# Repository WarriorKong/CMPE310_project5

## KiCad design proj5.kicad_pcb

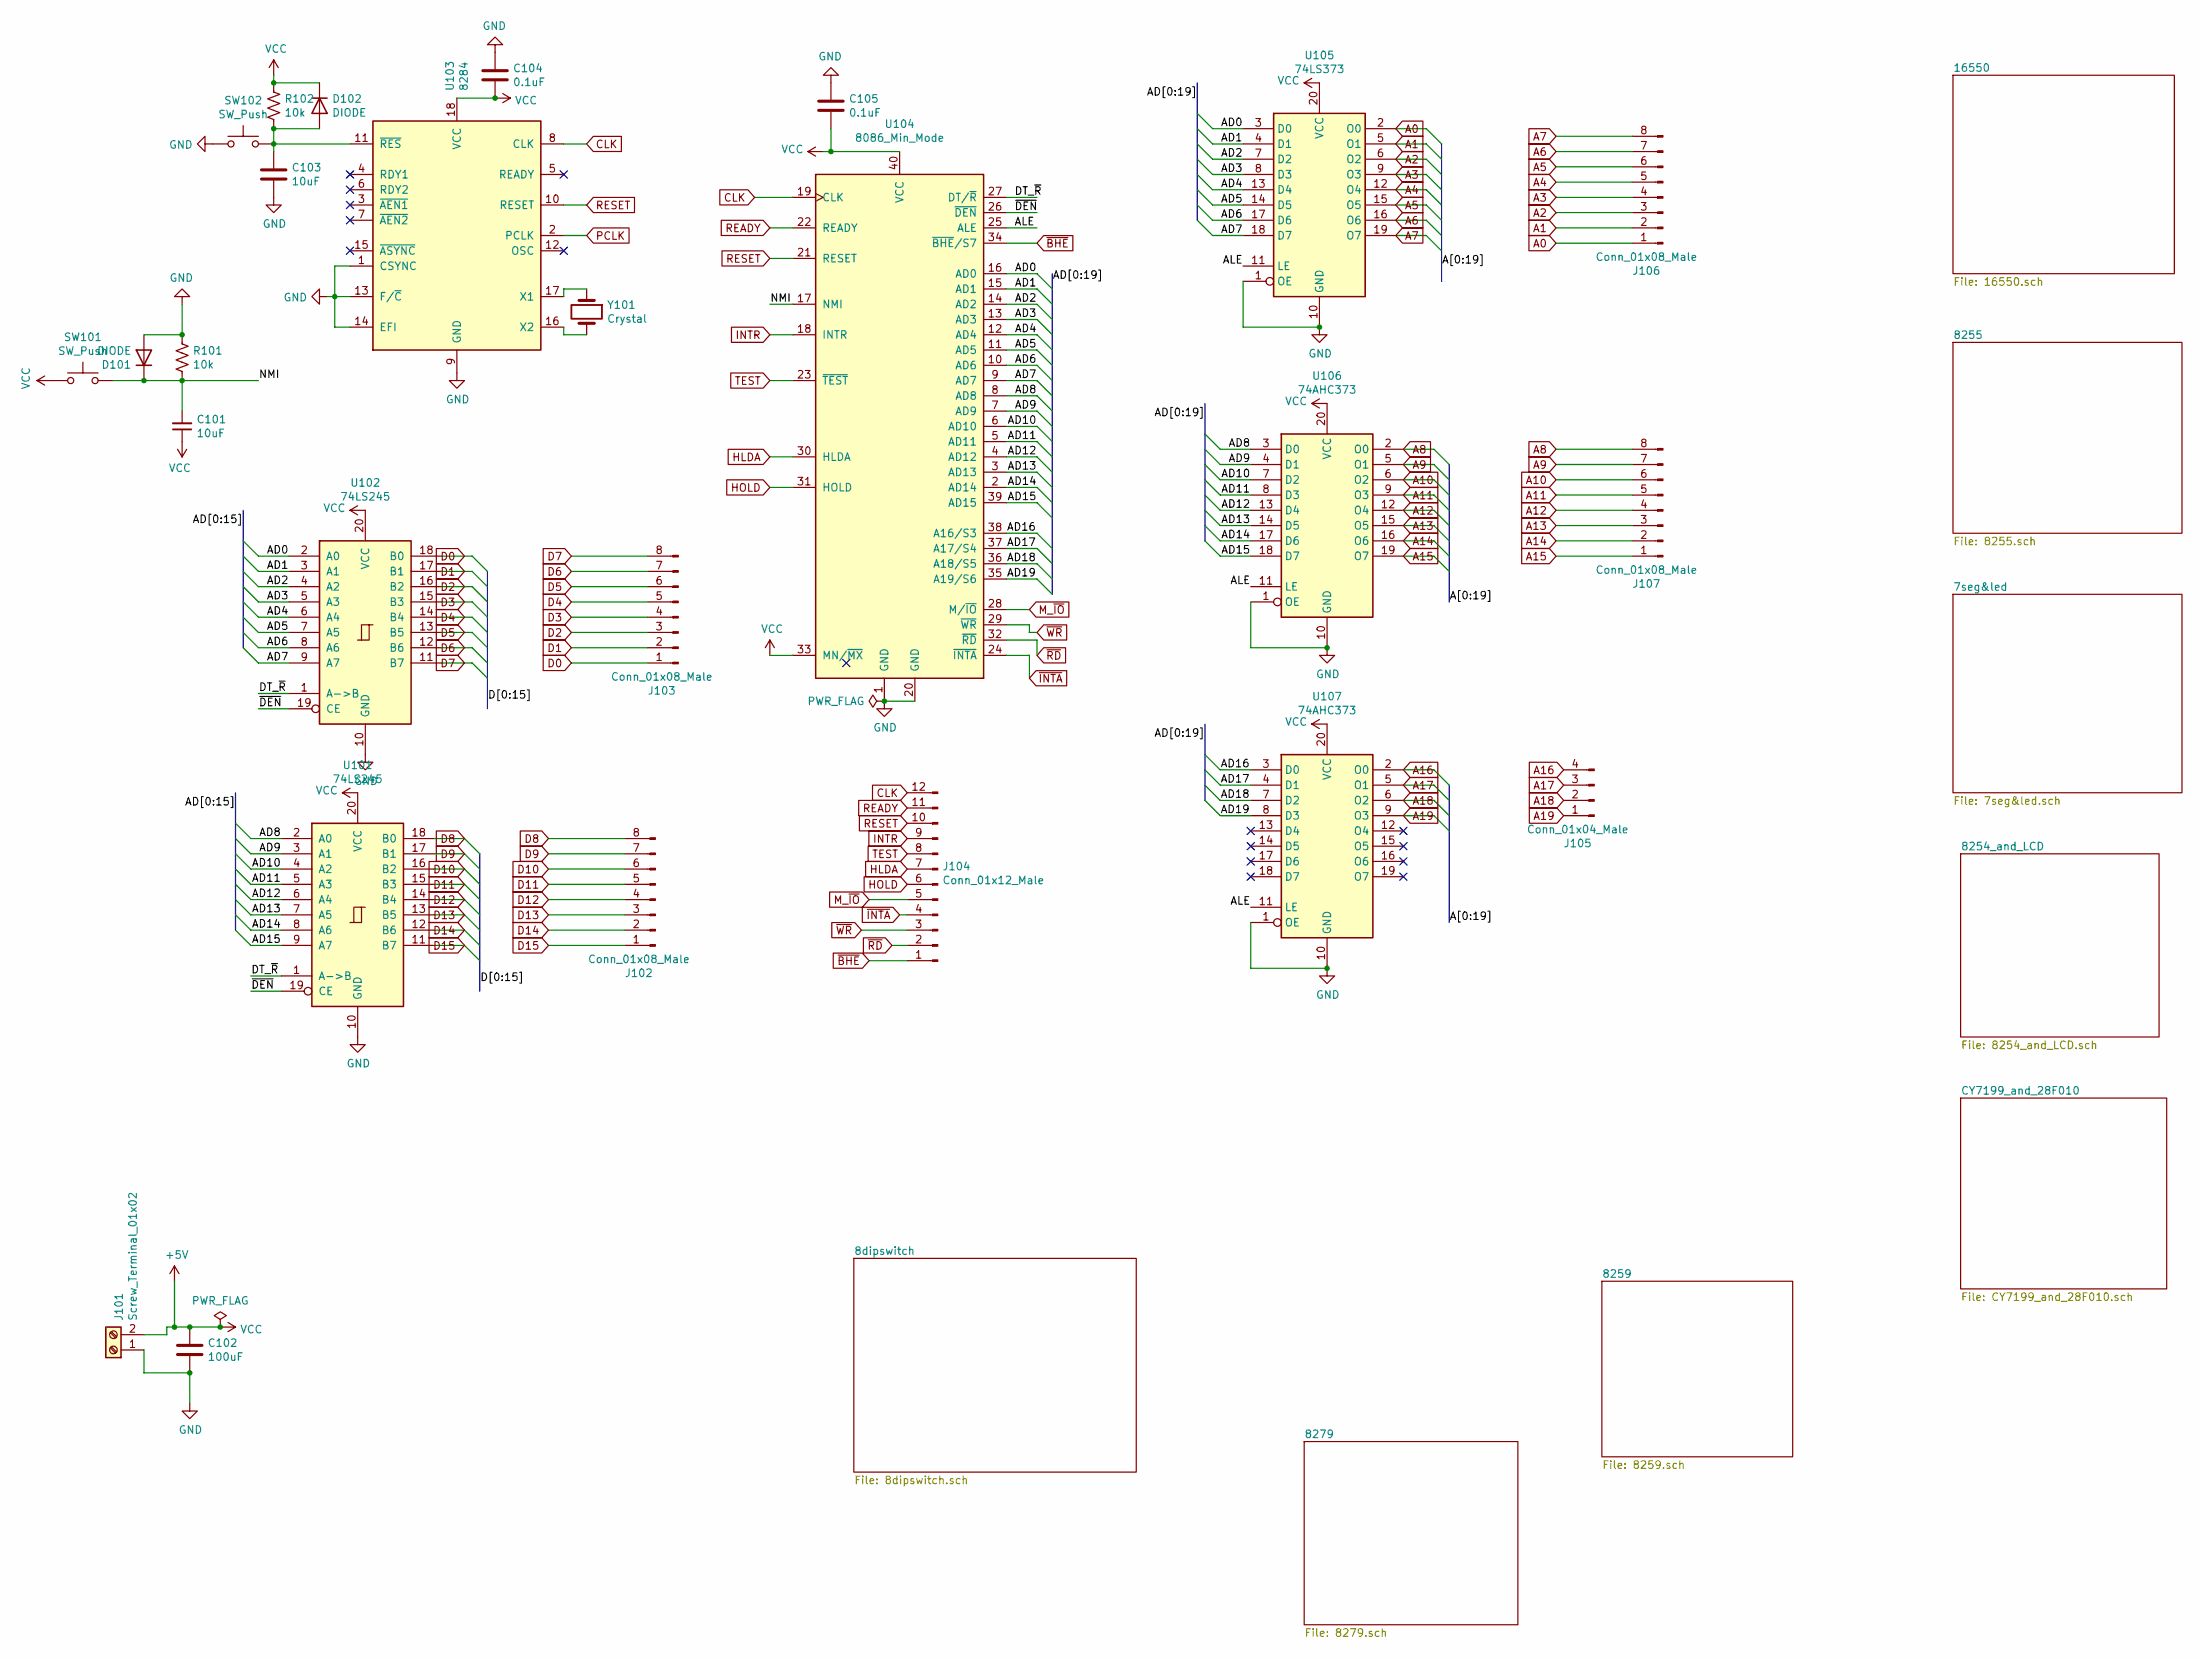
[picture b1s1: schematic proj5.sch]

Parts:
C101, C103: 10uF; CP_Elec_5x3
C102: 100uF; CP_Elec_8x5.4
C104, C105: 0.1uF; CP_Elec_3x5.3
D101, D102: DIODE; D_0402_1005Metric
J101: Screw_Terminal_01x02; TerminalBlock_Phoenix_MKDS-1,5-2-5.08_1x02_P5.08mm_Horizont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
J102, J103, J106, J107: Conn_01x08_Male; JST_GH_BM08B-GHS-TBT_1x08-1MP_P1.25mm_Vertical
J104: Conn_01x12_Male; JST_GH_BM12B-GHS-TBT_1x12-1MP_P1.25mm_Vertical
J105: Conn_01x04_Male; JST_GH_BM04B-GHS-TBT_1x04-1MP_P1.25mm_Vertical
R101, R102: 10k; R_0402_1005Metric
SW101, SW102: SW_Push; SW_SPST_B3U-1000P
U101, U102: 74LS245; DIP-20_W7.62mm_SMDSocket_SmallPads
U103: 8284; DIP-18_W7.62mm
U104: 8086_Min_Mode; DIP-40_W15.24mm
U105: 74LS373; DIP-20_W7.62mm_SMDSocket_SmallPads
U106, U107: 74AHC373; DIP-20_W7.62mm_SMDSocket_SmallPads
Y101: Crystal; Crystal_AT310_D3.0mm_L10.0mm_Horizontal

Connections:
+5V: C101.1, C102.1, C104.2, C105.2, D102.2 (K), J101.2, R102.1, SW101.1, U101.20 (VCC), U102.20 (VCC), U103.18 (VCC), U104.33 (MN/~MX~), U104.40 (VCC), U105.20 (VCC), U106.20 (VCC), U107.20 (VCC); also elsewhere on the board
/AD0: U102.2 (A0), U104.16 (AD0), U105.3 (D0)
/AD1: U102.3 (A1), U104.15 (AD1), U105.4 (D1)
/AD2: U102.4 (A2), U104.14 (AD2), U105.7 (D2)
/AD3: U102.5 (A3), U104.13 (AD3), U105.8 (D3)
/AD4: U102.6 (A4), U104.12 (AD4), U105.13 (D4)
/AD5: U102.7 (A5), U104.11 (AD5), U105.14 (D5)
/AD6: U102.8 (A6), U104.10 (AD6), U105.17 (D6)
/AD7: U102.9 (A7), U104.9 (AD7), U105.18 (D7)
/AD8: U101.2 (A0), U104.8 (AD8), U106.3 (D0)
/AD9: U101.3 (A1), U104.7 (AD9), U106.4 (D1)
/AD10: U101.4 (A2), U104.6 (AD10), U106.7 (D2)
/AD11: U101.5 (A3), U104.5 (AD11), U106.8 (D3)
/AD12: U101.6 (A4), U104.4 (AD12), U106.13 (D4)
/AD13: U101.7 (A5), U104.3 (AD13), U106.14 (D5)
/AD14: U101.8 (A6), U104.2 (AD14), U106.17 (D6)
/AD15: U101.9 (A7), U104.39 (AD15), U106.18 (D7)
/AD16: U104.38 (A16/S3), U107.3 (D0)
/AD17: U104.37 (A17/S4), U107.4 (D1)
/AD18: U104.36 (A18/S5), U107.7 (D2)
/AD19: U104.35 (A19/S6), U107.8 (D3)
/ALE: U104.25 (ALE), U105.11 (LE), U106.11 (LE), U107.11 (LE)
/DT_~R: U101.1 (A->B), U102.1 (A->B), U104.27 (DT/~R~)
/NMI: C101.2, D101.2 (K), R101.2, SW101.2, U104.17 (NMI)
/~DEN: U101.19 (CE), U102.19 (CE), U104.26 (~DEN~)
A0: J106.1, U105.2 (O0); also elsewhere on the board
A1: J106.2, U105.5 (O1); also elsewhere on the board
A2: J106.3, U105.6 (O2); also elsewhere on the board
A3: J106.4, U105.9 (O3); also elsewhere on the board
A4: J106.5, U105.12 (O4); also elsewhere on the board
A5: J106.6, U105.15 (O5); also elsewhere on the board
A6: J106.7, U105.16 (O6); also elsewhere on the board
A7: J106.8, U105.19 (O7); also elsewhere on the board
A8: J107.8, U106.2 (O0); also elsewhere on the board
A9: J107.7, U106.5 (O1); also elsewhere on the board
A10: J107.6, U106.6 (O2); also elsewhere on the board
A11: J107.5, U106.9 (O3); also elsewhere on the board
A12: J107.4, U106.12 (O4); also elsewhere on the board
A13: J107.3, U106.15 (O5); also elsewhere on the board
A14: J107.2, U106.16 (O6); also elsewhere on the board
A15: J107.1, U106.19 (O7); also elsewhere on the board
A16: J105.4, U107.2 (O0); also elsewhere on the board
A17: J105.3, U107.5 (O1); also elsewhere on the board
A18: J105.2, U107.6 (O2); also elsewhere on the board
A19: J105.1, U107.9 (O3); also elsewhere on the board
CLK: J104.12, U103.8 (CLK), U104.19 (CLK)
D0: J103.1, U102.18 (B0); also elsewhere on the board
D1: J103.2, U102.17 (B1); also elsewhere on the board
D2: J103.3, U102.16 (B2); also elsewhere on the board
D3: J103.4, U102.15 (B3); also elsewhere on the board
D4: J103.5, U102.14 (B4); also elsewhere on the board
D5: J103.6, U102.13 (B5); also elsewhere on the board
D6: J103.7, U102.12 (B6); also elsewhere on the board
D7: J103.8, U102.11 (B7); also elsewhere on the board
D8: J102.8, U101.18 (B0)
D9: J102.7, U101.17 (B1)
D10: J102.6, U101.16 (B2)
D11: J102.5, U101.15 (B3)
D12: J102.4, U101.14 (B4)
D13: J102.3, U101.13 (B5)
D14: J102.2, U101.12 (B6)
D15: J102.1, U101.11 (B7)
GND: C102.2, C103.2, C104.1, C105.1, D101.1 (A), J101.1, R101.1, SW102.1, U101.10 (GND), U102.10 (GND), U103.1 (CSYNC), U103.9 (GND), U103.13 (F/~C~), U103.14 (EFI), U104.1 (GND), U104.20 (GND), U105.1 (OE), U105.10 (GND), U106.1 (OE), U106.10 (GND), U107.1 (OE), U107.10 (GND); also elsewhere on the board
HLDA: J104.7, U104.30 (HLDA)
HOLD: J104.6, U104.31 (HOLD)
INTR: J104.9, U104.18 (INTR); also elsewhere on the board
M_~IO: J104.5, U104.28 (M/~IO~); also elsewhere on the board
unnamed: C103.1, D102.1 (A), R102.2, SW102.2, U103.11 (~RES~)
unnamed: U103.16 (X2), Y101.2
unnamed: U103.17 (X1), Y101.1
PCLK: U103.2 (PCLK); also elsewhere on the board
READY: J104.11, U104.22 (READY)
RESET: J104.10, U103.10 (RESET), U104.21 (RESET); also elsewhere on the board
TEST: J104.8, U104.23 (~TEST~)
~BHE: J104.1, U104.34 (~BHE~/S7); also elsewhere on the board
~INTA: J104.4, U104.24 (~INTA~); also elsewhere on the board
~RD: J104.2, U104.32 (~RD~); also elsewhere on the board
~WR: J104.3, U104.29 (~WR~); also elsewhere on the board

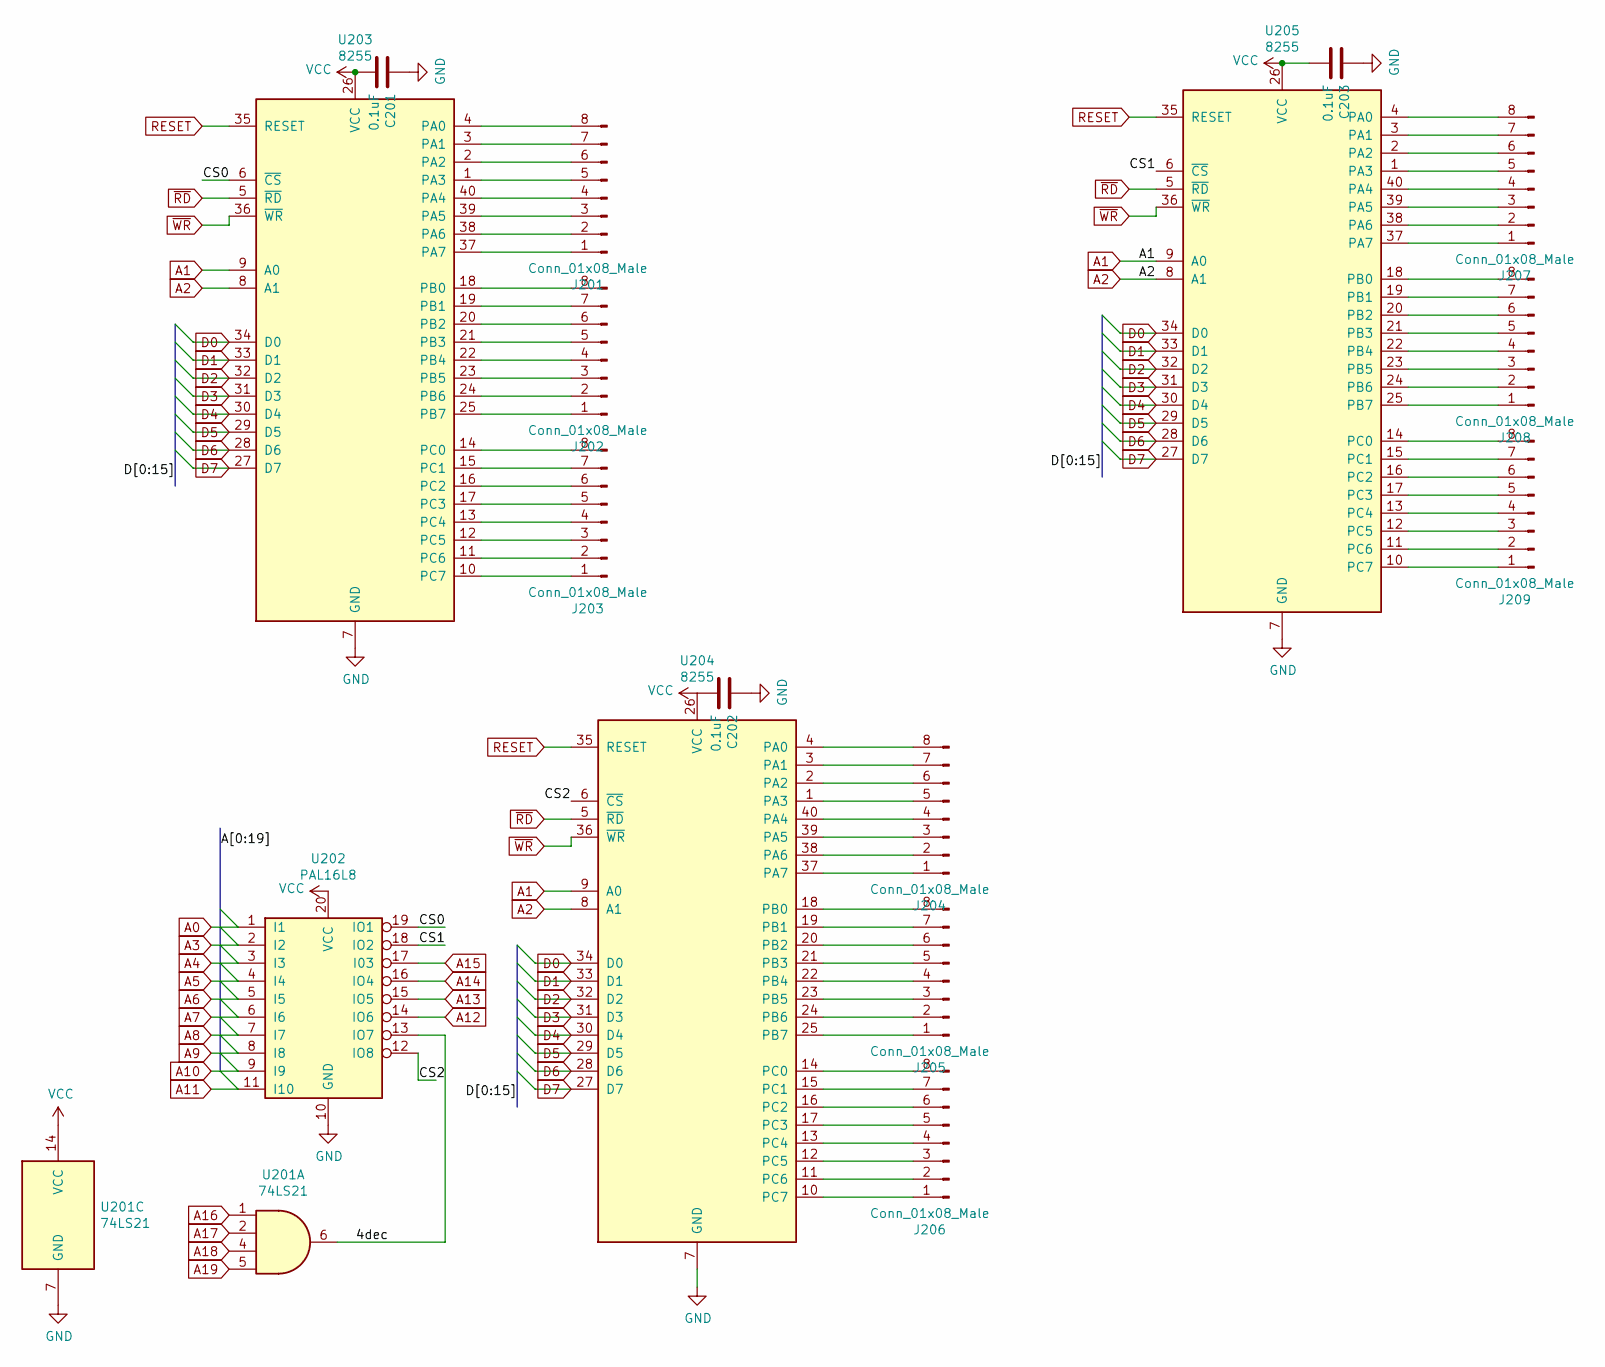
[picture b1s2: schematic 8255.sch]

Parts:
C201, C202, C203: 0.1uF; CP_Elec_3x5.3
J201, J202, J203, J204, J205, J206, J207, J208, J209: Conn_01x08_Male; JST_GH_BM08B-GHS-TBT_1x08-1MP_P1.25mm_Vertical
U201: 74LS21; DIP-14_W7.62mm_SMDSocket_SmallPads
U202: PAL16L8; DIP-20_W8.89mm_SMDSocket_LongPads
U203, U204, U205: 8255; DIP-40_W15.24mm

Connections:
+5V: C201.2, C202.2, C203.2, U201.14 (VCC), U202.20 (VCC), U203.26 (VCC), U204.26 (VCC), U205.26 (VCC); also elsewhere on the board
/8255/4dec: U201.6, U202.13 (IO7)
/8255/CS0: U202.19 (IO1), U203.6 (~CS~)
/8255/CS1: U202.18 (IO2), U205.6 (~CS~)
/8255/CS2: U202.12 (IO8), U204.6 (~CS~)
A0: U202.1 (I1); also elsewhere on the board
A1: U203.9 (A0), U204.9 (A0), U205.9 (A0); also elsewhere on the board
A2: U203.8 (A1), U204.8 (A1), U205.8 (A1); also elsewhere on the board
A3: U202.2 (I2); also elsewhere on the board
A4: U202.3 (I3); also elsewhere on the board
A5: U202.4 (I4); also elsewhere on the board
A6: U202.5 (I5); also elsewhere on the board
A7: U202.6 (I6); also elsewhere on the board
A8: U202.7 (I7); also elsewhere on the board
A9: U202.8 (I8); also elsewhere on the board
A10: U202.9 (I9); also elsewhere on the board
A11: U202.11 (I10); also elsewhere on the board
A12: U202.14 (IO6); also elsewhere on the board
A13: U202.15 (IO5); also elsewhere on the board
A14: U202.16 (IO4); also elsewhere on the board
A15: U202.17 (I03); also elsewhere on the board
A16: U201.1; also elsewhere on the board
A17: U201.2; also elsewhere on the board
A18: U201.4; also elsewhere on the board
A19: U201.5; also elsewhere on the board
D0: U203.34 (D0), U204.34 (D0), U205.34 (D0); also elsewhere on the board
D1: U203.33 (D1), U204.33 (D1), U205.33 (D1); also elsewhere on the board
D2: U203.32 (D2), U204.32 (D2), U205.32 (D2); also elsewhere on the board
D3: U203.31 (D3), U204.31 (D3), U205.31 (D3); also elsewhere on the board
D4: U203.30 (D4), U204.30 (D4), U205.30 (D4); also elsewhere on the board
D5: U203.29 (D5), U204.29 (D5), U205.29 (D5); also elsewhere on the board
D6: U203.28 (D6), U204.28 (D6), U205.28 (D6); also elsewhere on the board
D7: U203.27 (D7), U204.27 (D7), U205.27 (D7); also elsewhere on the board
GND: C201.1, C202.1, C203.1, U201.7 (GND), U202.10 (GND), U203.7 (GND), U204.7 (GND), U205.7 (GND); also elsewhere on the board
unnamed: J201.1, U203.37 (PA7)
unnamed: J201.2, U203.38 (PA6)
unnamed: J201.3, U203.39 (PA5)
unnamed: J201.4, U203.40 (PA4)
unnamed: J201.5, U203.1 (PA3)
unnamed: J201.6, U203.2 (PA2)
unnamed: J201.7, U203.3 (PA1)
unnamed: J201.8, U203.4 (PA0)
unnamed: J202.1, U203.25 (PB7)
unnamed: J202.2, U203.24 (PB6)
unnamed: J202.3, U203.23 (PB5)
unnamed: J202.4, U203.22 (PB4)
unnamed: J202.5, U203.21 (PB3)
unnamed: J202.6, U203.20 (PB2)
unnamed: J202.7, U203.19 (PB1)
unnamed: J202.8, U203.18 (PB0)
unnamed: J203.1, U203.10 (PC7)
unnamed: J203.2, U203.11 (PC6)
unnamed: J203.3, U203.12 (PC5)
unnamed: J203.4, U203.13 (PC4)
unnamed: J203.5, U203.17 (PC3)
unnamed: J203.6, U203.16 (PC2)
unnamed: J203.7, U203.15 (PC1)
unnamed: J203.8, U203.14 (PC0)
unnamed: J204.1, U204.37 (PA7)
unnamed: J204.2, U204.38 (PA6)
unnamed: J204.3, U204.39 (PA5)
unnamed: J204.4, U204.40 (PA4)
unnamed: J204.5, U204.1 (PA3)
unnamed: J204.6, U204.2 (PA2)
unnamed: J204.7, U204.3 (PA1)
unnamed: J204.8, U204.4 (PA0)
unnamed: J205.1, U204.25 (PB7)
unnamed: J205.2, U204.24 (PB6)
unnamed: J205.3, U204.23 (PB5)
unnamed: J205.4, U204.22 (PB4)
unnamed: J205.5, U204.21 (PB3)
unnamed: J205.6, U204.20 (PB2)
unnamed: J205.7, U204.19 (PB1)
unnamed: J205.8, U204.18 (PB0)
unnamed: J206.1, U204.10 (PC7)
unnamed: J206.2, U204.11 (PC6)
unnamed: J206.3, U204.12 (PC5)
unnamed: J206.4, U204.13 (PC4)
unnamed: J206.5, U204.17 (PC3)
unnamed: J206.6, U204.16 (PC2)
unnamed: J206.7, U204.15 (PC1)
unnamed: J206.8, U204.14 (PC0)
unnamed: J207.1, U205.37 (PA7)
unnamed: J207.2, U205.38 (PA6)
unnamed: J207.3, U205.39 (PA5)
unnamed: J207.4, U205.40 (PA4)
unnamed: J207.5, U205.1 (PA3)
unnamed: J207.6, U205.2 (PA2)
unnamed: J207.7, U205.3 (PA1)
unnamed: J207.8, U205.4 (PA0)
unnamed: J208.1, U205.25 (PB7)
unnamed: J208.2, U205.24 (PB6)
unnamed: J208.3, U205.23 (PB5)
unnamed: J208.4, U205.22 (PB4)
unnamed: J208.5, U205.21 (PB3)
unnamed: J208.6, U205.20 (PB2)
unnamed: J208.7, U205.19 (PB1)
unnamed: J208.8, U205.18 (PB0)
unnamed: J209.1, U205.10 (PC7)
unnamed: J209.2, U205.11 (PC6)
unnamed: J209.3, U205.12 (PC5)
unnamed: J209.4, U205.13 (PC4)
unnamed: J209.5, U205.17 (PC3)
unnamed: J209.6, U205.16 (PC2)
unnamed: J209.7, U205.15 (PC1)
unnamed: J209.8, U205.14 (PC0)
RESET: U203.35 (RESET), U204.35 (RESET), U205.35 (RESET); also elsewhere on the board
~RD: U203.5 (~RD~), U204.5 (~RD~), U205.5 (~RD~); also elsewhere on the board
~WR: U203.36 (~WR~), U204.36 (~WR~), U205.36 (~WR~); also elsewhere on the board

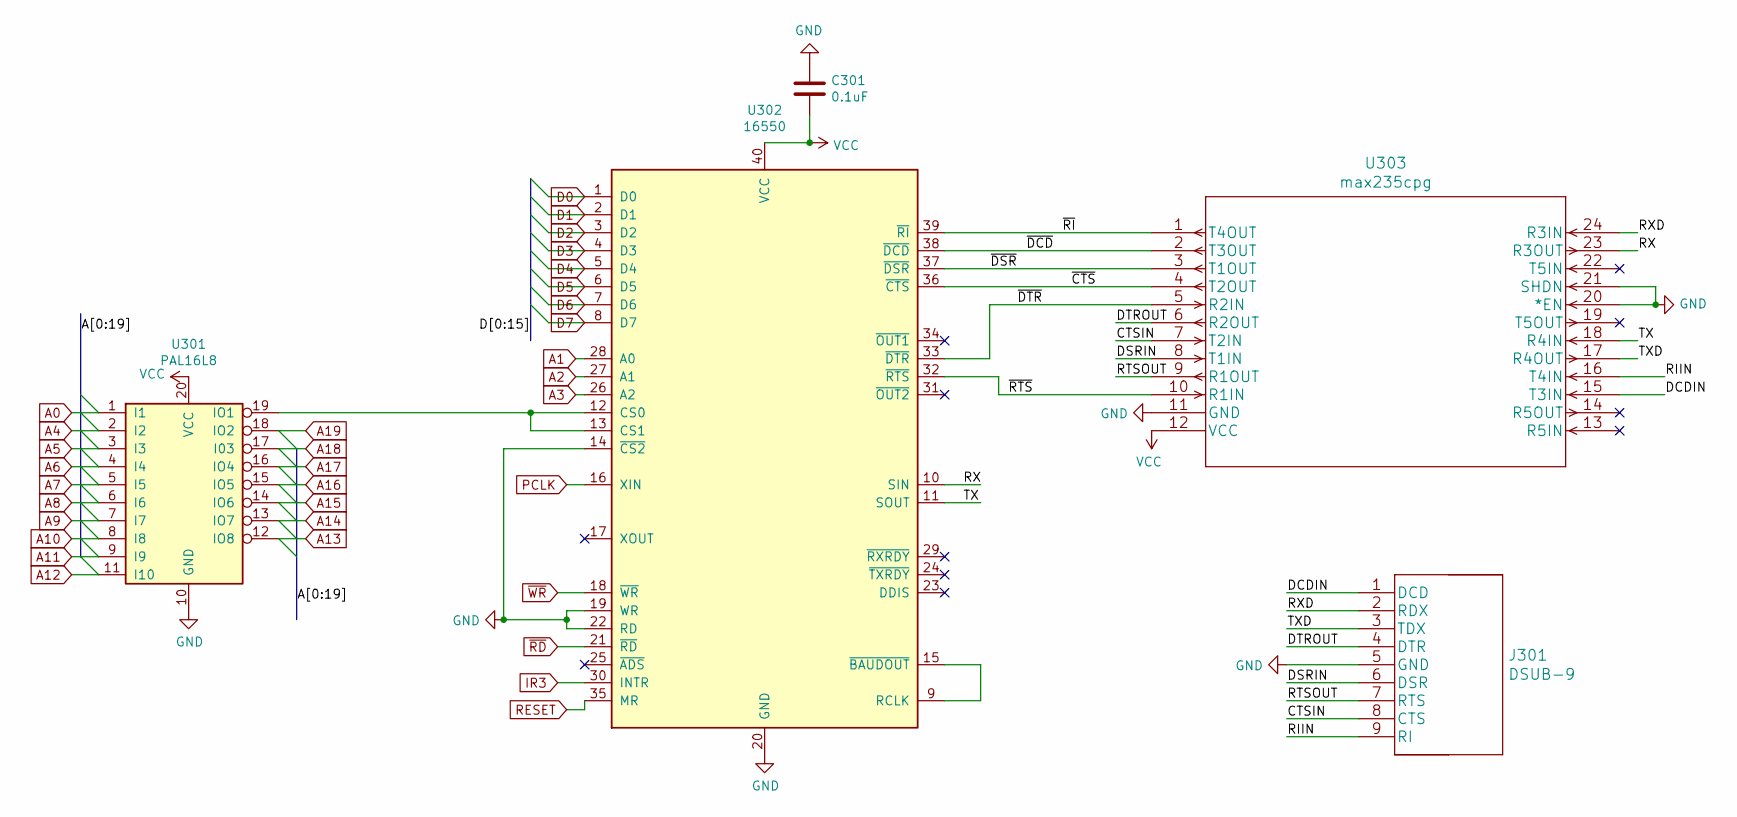
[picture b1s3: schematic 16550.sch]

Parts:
C301: 0.1uF; CP_Elec_3x5.3
J301: DSUB-9
U301: PAL16L8; DIP-20_W7.62mm_SMDSocket_SmallPads
U302: 16550; DIP-40_W15.24mm
U303: max235cpg

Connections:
+5V: C301.2, U301.20 (VCC), U302.40 (VCC), U303.12 (VCC); also elsewhere on the board
/16550/CTSIN: J301.8 (CTS), U303.7 (T2IN)
/16550/DCDIN: J301.1 (DCD), U303.15 (T3IN)
/16550/DSRIN: J301.6 (DSR), U303.8 (T1IN)
/16550/DTROUT: J301.4 (DTR), U303.6 (R2OUT)
/16550/RIIN: J301.9 (RI), U303.16 (T4IN)
/16550/RTSOUT: J301.7 (RTS), U303.9 (R1OUT)
/16550/RX: U302.10 (SIN), U303.23 (R3OUT)
/16550/RXD: J301.2 (RDX), U303.24 (R3IN)
/16550/TX: U302.11 (SOUT), U303.18 (R4IN)
/16550/TXD: J301.3 (TDX), U303.17 (R4OUT)
/16550/~CTS: U302.36 (~CTS~), U303.4 (T2OUT)
/16550/~DCD: U302.38 (~DCD~), U303.2 (T3OUT)
/16550/~DSR: U302.37 (~DSR~), U303.3 (T1OUT)
/16550/~DTR: U302.33 (~DTR~), U303.5 (R2IN)
/16550/~RI: U302.39 (~RI~), U303.1 (T4OUT)
/16550/~RTS: U302.32 (~RTS~), U303.10 (R1IN)
A0: U301.1 (I1); also elsewhere on the board
A1: U302.28 (A0); also elsewhere on the board
A2: U302.27 (A1); also elsewhere on the board
A3: U302.26 (A2); also elsewhere on the board
A4: U301.2 (I2); also elsewhere on the board
A5: U301.3 (I3); also elsewhere on the board
A6: U301.4 (I4); also elsewhere on the board
A7: U301.5 (I5); also elsewhere on the board
A8: U301.6 (I6); also elsewhere on the board
A9: U301.7 (I7); also elsewhere on the board
A10: U301.8 (I8); also elsewhere on the board
A11: U301.9 (I9); also elsewhere on the board
A12: U301.11 (I10); also elsewhere on the board
A13: U301.12 (IO8); also elsewhere on the board
A14: U301.13 (IO7); also elsewhere on the board
A15: U301.14 (IO6); also elsewhere on the board
A16: U301.15 (IO5); also elsewhere on the board
A17: U301.16 (IO4); also elsewhere on the board
A18: U301.17 (I03); also elsewhere on the board
A19: U301.18 (IO2); also elsewhere on the board
D0: U302.1 (D0); also elsewhere on the board
D1: U302.2 (D1); also elsewhere on the board
D2: U302.3 (D2); also elsewhere on the board
D3: U302.4 (D3); also elsewhere on the board
D4: U302.5 (D4); also elsewhere on the board
D5: U302.6 (D5); also elsewhere on the board
D6: U302.7 (D6); also elsewhere on the board
D7: U302.8 (D7); also elsewhere on the board
GND: C301.1, J301.5 (GND), U301.10 (GND), U302.14 (~CS2~), U302.19 (WR), U302.20 (GND), U302.22 (RD), U303.11 (GND), U303.20 (*EN), U303.21 (SHDN); also elsewhere on the board
IR3: U302.30 (INTR); also elsewhere on the board
unnamed: U301.19 (IO1), U302.12 (CS0), U302.13 (CS1)
unnamed: U302.9 (RCLK), U302.15 (~BAUDOUT~)
PCLK: U302.16 (XIN); also elsewhere on the board
RESET: U302.35 (MR); also elsewhere on the board
~RD: U302.21 (~RD~); also elsewhere on the board
~WR: U302.18 (~WR~); also elsewhere on the board

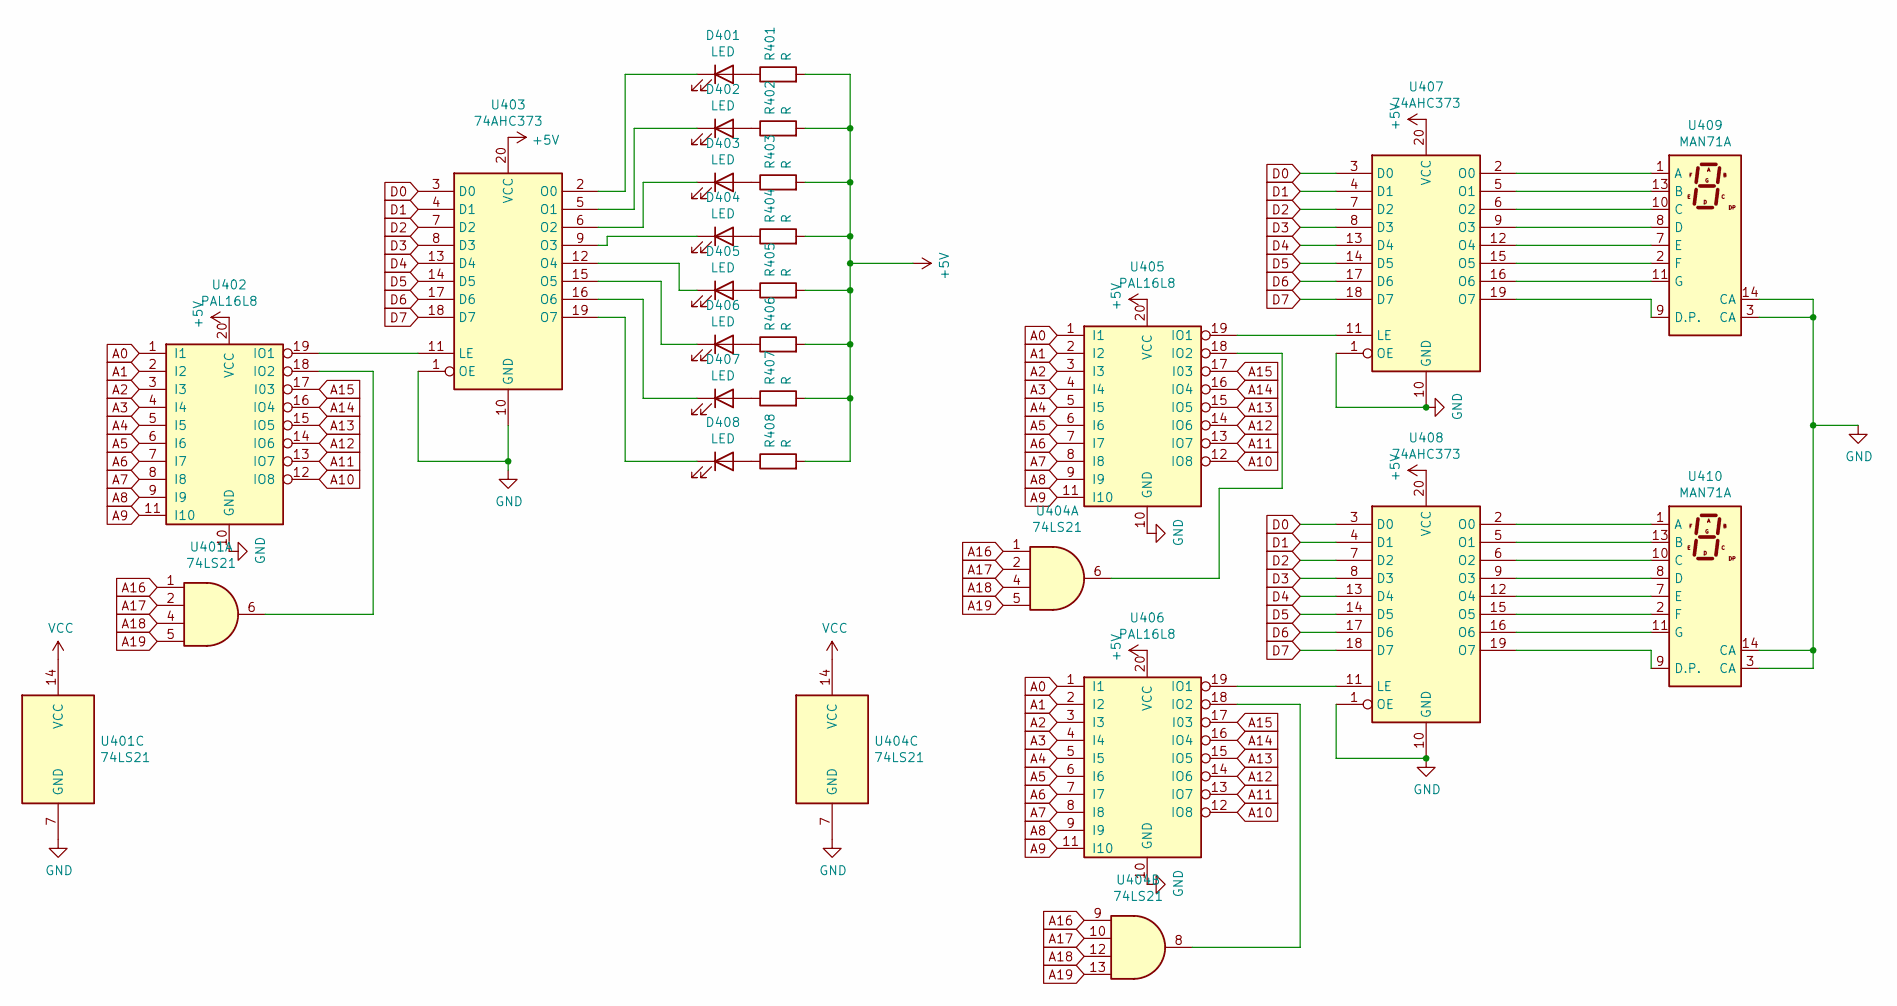
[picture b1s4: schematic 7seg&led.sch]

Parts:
D401, D402, D403, D404, D405, D406, D407, D408: LED; LED_1812_4532Metric
R401, R402, R403, R404, R405, R406, R407, R408: R; R_0402_1005Metric
U401, U404: 74LS21; DIP-14_W7.62mm_SMDSocket_SmallPads
U402, U405, U406: PAL16L8; DIP-20_W7.62mm_SMDSocket_SmallPads
U403, U407, U408: 74AHC373; DIP-20_W7.62mm_SMDSocket_SmallPads
U409, U410: MAN71A

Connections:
+5V: R401.2, R402.2, R403.2, R404.2, R405.2, R406.2, R407.2, R408.2, U401.14 (VCC), U402.20 (VCC), U403.20 (VCC), U404.14 (VCC), U405.20 (VCC), U406.20 (VCC), U407.20 (VCC), U408.20 (VCC); also elsewhere on the board
A0: U402.1 (I1), U405.1 (I1), U406.1 (I1); also elsewhere on the board
A1: U402.2 (I2), U405.2 (I2), U406.2 (I2); also elsewhere on the board
A2: U402.3 (I3), U405.3 (I3), U406.3 (I3); also elsewhere on the board
A3: U402.4 (I4), U405.4 (I4), U406.4 (I4); also elsewhere on the board
A4: U402.5 (I5), U405.5 (I5), U406.5 (I5); also elsewhere on the board
A5: U402.6 (I6), U405.6 (I6), U406.6 (I6); also elsewhere on the board
A6: U402.7 (I7), U405.7 (I7), U406.7 (I7); also elsewhere on the board
A7: U402.8 (I8), U405.8 (I8), U406.8 (I8); also elsewhere on the board
A8: U402.9 (I9), U405.9 (I9), U406.9 (I9); also elsewhere on the board
A9: U402.11 (I10), U405.11 (I10), U406.11 (I10); also elsewhere on the board
A10: U402.12 (IO8), U405.12 (IO8), U406.12 (IO8); also elsewhere on the board
A11: U402.13 (IO7), U405.13 (IO7), U406.13 (IO7); also elsewhere on the board
A12: U402.14 (IO6), U405.14 (IO6), U406.14 (IO6); also elsewhere on the board
A13: U402.15 (IO5), U405.15 (IO5), U406.15 (IO5); also elsewhere on the board
A14: U402.16 (IO4), U405.16 (IO4), U406.16 (IO4); also elsewhere on the board
A15: U402.17 (I03), U405.17 (I03), U406.17 (I03); also elsewhere on the board
A16: U401.1, U404.1, U404.9; also elsewhere on the board
A17: U401.2, U404.2, U404.10; also elsewhere on the board
A18: U401.4, U404.4, U404.12; also elsewhere on the board
A19: U401.5, U404.5, U404.13; also elsewhere on the board
D0: U403.3 (D0), U407.3 (D0), U408.3 (D0); also elsewhere on the board
D1: U403.4 (D1), U407.4 (D1), U408.4 (D1); also elsewhere on the board
D2: U403.7 (D2), U407.7 (D2), U408.7 (D2); also elsewhere on the board
D3: U403.8 (D3), U407.8 (D3), U408.8 (D3); also elsewhere on the board
D4: U403.13 (D4), U407.13 (D4), U408.13 (D4); also elsewhere on the board
D5: U403.14 (D5), U407.14 (D5), U408.14 (D5); also elsewhere on the board
D6: U403.17 (D6), U407.17 (D6), U408.17 (D6); also elsewhere on the board
D7: U403.18 (D7), U407.18 (D7), U408.18 (D7); also elsewhere on the board
GND: U401.7 (GND), U402.10 (GND), U403.1 (OE), U403.10 (GND), U404.7 (GND), U405.10 (GND), U406.10 (GND), U407.1 (OE), U407.10 (GND), U408.1 (OE), U408.10 (GND), U409.3 (CA), U409.14 (CA), U410.3 (CA), U410.14 (CA); also elsewhere on the board
unnamed: D401.1 (K), U403.2 (O0)
unnamed: D401.2 (A), R401.1
unnamed: D402.1 (K), U403.5 (O1)
unnamed: D402.2 (A), R402.1
unnamed: D403.1 (K), U403.6 (O2)
unnamed: D403.2 (A), R403.1
unnamed: D404.1 (K), U403.9 (O3)
unnamed: D404.2 (A), R404.1
unnamed: D405.1 (K), U403.12 (O4)
unnamed: D405.2 (A), R405.1
unnamed: D406.1 (K), U403.15 (O5)
unnamed: D406.2 (A), R406.1
unnamed: D407.1 (K), U403.16 (O6)
unnamed: D407.2 (A), R407.1
unnamed: D408.1 (K), U403.19 (O7)
unnamed: D408.2 (A), R408.1
unnamed: U401.6, U402.18 (IO2)
unnamed: U402.19 (IO1), U403.11 (LE)
unnamed: U404.6, U405.18 (IO2)
unnamed: U404.8, U406.18 (IO2)
unnamed: U405.19 (IO1), U407.11 (LE)
unnamed: U406.19 (IO1), U408.11 (LE)
unnamed: U407.2 (O0), U409.1 (A)
unnamed: U407.5 (O1), U409.13 (B)
unnamed: U407.6 (O2), U409.10 (C)
unnamed: U407.9 (O3), U409.8 (D)
unnamed: U407.12 (O4), U409.7 (E)
unnamed: U407.15 (O5), U409.2 (F)
unnamed: U407.16 (O6), U409.11 (G)
unnamed: U407.19 (O7), U409.9 (D.P.)
unnamed: U408.2 (O0), U410.1 (A)
unnamed: U408.5 (O1), U410.13 (B)
unnamed: U408.6 (O2), U410.10 (C)
unnamed: U408.9 (O3), U410.8 (D)
unnamed: U408.12 (O4), U410.7 (E)
unnamed: U408.15 (O5), U410.2 (F)
unnamed: U408.16 (O6), U410.11 (G)
unnamed: U408.19 (O7), U410.9 (D.P.)

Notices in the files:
parts and their libraries:
Copyright 2016 Accelerated Designs. All rights reserved.
